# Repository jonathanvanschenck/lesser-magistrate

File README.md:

#  The Lesser Magistrate
A collection of Electrical and Mechanical Schematics for the IOC Lesser Magistrate Quizzing System

Schematics, PCB Files, BOM and 3D printing files are [available here](https://github.com/jonathanvanschenck/lesser-magistrate).

To find more information or get involved with Christian Bible Quizzing (CBQ), [click here](https://cbqz.org).

## Philosophy of Design
Heretofore, bible quizzing has had a fairly high barrier to entry; whether it be complicated rulebooks, distinct cultural practices or (of relevance here) expensive supplies. This project
seeks to address that third barrier by providing a low-cost, high-performance quizzing buzzer system, which can built by a reasonably competent individual. Unlike existing systems, we need
to meet the following design requirements:

  - Low cost and easily available parts
  - Easily manufactureable without special tooling
  - Is modular in design (e.g. individual components are easily and cheaply replaceable)
  - Can support up to 15 simultaneous participants

## Build Instructions
A Lesser Magistrate set can be built with a varying number of triggers depending on your needs. Throughout this documentation, examples are given for three common configurations:

- **16 triggers** — the maximum supported: 3 teams of 5 quizzers each, plus 1 trigger reserved for the quiz magistrate.
- **10 triggers** — the typical arrangement for a CBQ quiz: 3 teams of 3 quizzers each, plus 1 for the quiz magistrate.
- **12 triggers** — a 10-trigger set with 2 spares, useful to have on hand in case of hardware failure during a tournament.

If you have recieved a build kit, you should already have all the raw materials to build a lesser magistrate, including electrical components, 3d printed enclosures and hardware. In this case, you will only need a few tools to help during the build:
  - A Soldering Iron (literally anything will work here -- you don't need to spend tons of money on this unless you plan to make a lot of units)
  - Lead-free Solder (Again, literally anything will work here -- the amount of soldering on the project is pretty small so you won't run out)
  - Allen Wrench
  - Phillips head screw driver (long shaft)

### Video Guides and Examples

There is a video guide you can follow for step-by-step instructions on how to build your Lesser Magistrate system:

- https://www.youtube.com/watch?v=u-B20jy8v2o&list=PL-Vn05Kf5ezxIfupx7_Z1d6l5HKGBeLW2

Here are additional example videos:

- https://youtu.be/reuCWvhqvTU
- https://youtu.be/7Vi3QWguprs
- https://youtu.be/mlhh7Sf7_HU
- https://youtu.be/uHA6wKbFMOs
- https://youtu.be/KhpSTn409PQ
- https://youtu.be/kogF7mJOyTQ

### Electrical Schematics

All electrical schematics are available in the [graphics](./graphics) directory, which can be helpful during assembly, particularly for those who are more electrically inclined. They match the boards made from the [gerber files](./gerber).

There are some additional tools which are very helpful during the build process; but are not strictly necessary:
  - Some elmers glue, or similar light adhesive
  - The assembly jigs, [see the 3d printer directory for details](./3d)

If you are interested in purchasing a Lesser Magistrate system (or any of the necessary components -- particularly the PCBs), contact [the author](https://github.com/jonathanvanschenck).

If you did *not* receive a kit, the next section will explain how to acquire all the necessary raw components.

### Ordering the Components Yourself
If you did not receive kit, you will need to acquire the raw materials. Broadly there are 3 categories of things you will need to purchase:

#### 1. Electrical Component
You will need to buy all the electrical components (meaning chips, resistors, connectors and wires). See the [components README](./components/README.md) for full part lists and Digikey shopping links for 16, 12, and 10 trigger set configurations.

#### 2. PCB
You will also need to buy the actual PCBs to soulder everything to. You can find the gerber files (the extension is `.zip`) in the `gerber` directory, with a [README](./gerber/README.md) for details. Always order from these files: they are the released version of each board, and the README there lists each board's version. You can use any PCB manufacturer you prefer, for example [PCBWay](https://www.pcbway.com/) -- in every case you cant just upload your gerber files and the website will walk you through the steps. Two things to note: (1) make sure to select HASL lead-free surface treatment to avoid lead exposure, use defaults for everything else (2) you will likely be required to order at least 5 of every board; but the boards are sufficiently cheap that shipping is frequently the majority of the PCB cost even when over-buying boards.

#### 3. Plastic Enclosures
You will also need to get plastic enclosures for all the electrical elements. All of this is done with a 3d printer. Many schools and libraries have 3d printers available to the students/members, so try asking around in your community to see if someone has access to a printer to help with this piece. There are also plenty of online services that you can upload a file to and have them print and ship it to you. Though, if you plan on making more than, like, 2 of these units -- just get a printer yourself. They are pretty cheap these days, can you can do a lot with them. Both [Bambu Labs](https://bambulab.com/en-us) and [Prusa Reaserch](https://www.prusa3d.com/) have mid-level and high-end hobbyist models in the $500-$1500 range.

However you plan on getting your prints, you will need the STL files in the [stl](./stl) directory -- see the README there for details.

## Contributing and Development
The Lesser Magistrate is a fully open sourced project, and as such contribution is encouraged! As such PRs are more than welcome, and we would love to hear about [any issues](https://github.com/jonathanvanschenck/lesser-magistrate/issues) you may run into. Feature requests are also encouraged -- though keep in mind features will only be included in this project if they conform to the Philosophy of Design described above. Finally, if you take this project and do something cool with it (like adding extra features not suitable to this design philosophy), we would love to hear about it so that we can add a link to your work in the section below!

The electrical design was originally drawn in DipTrace and is now developed in [KiCad](https://www.kicad.org/), with one project per board in the [kicad](./kicad) directory (see its [README](./kicad/README.md), which also explains how each board is versioned and released). The files in [gerber](./gerber) are KiCad releases; the [gerber README](./gerber/README.md) says where to find the original DipTrace exports. We are also working on an SMD variant of the LM/LMM/Trigger boards so they can be assembled by a pick-and-place machine.

Developer tooling (KiCad design checks, a crosstalk simulation, the generated parts tables, a DigiKey part-search CLI, and a KiCad MCP server for AI-assisted board design with Claude Code) is described in [DEVELOPMENT.md](./DEVELOPMENT.md).

## Related Projects

## Deuteronomy 6:5-7
Love the Lord your God with all your heart and with all your soul and with all your strength.
These commandments that I give you today are to be on your hearts.
Impress them on your children. Talk about them when you sit at home and when you walk along the road, when you lie down and when you get up.

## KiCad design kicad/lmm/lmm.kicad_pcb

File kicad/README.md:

# KiCad Projects

The electrical design for the Lesser Magistrate, in KiCad 10. One project per board, plus one shared library:

```
kicad/
├── libraries/
│   ├── lesser-magistrate.kicad_sym   # symbols for the parts used on the boards
│   ├── lesser-magistrate.pretty/     # footprints for the parts used on the boards
│   └── lesser-magistrate.3dshapes/   # manufacturer 3D models KiCad doesn't ship
├── lm/        # LM: main quiz-magistrate controller board  (1 per set)
├── lmm/       # LMM: team module / breakout board          (1 per team)
└── trigger/   # Trigger: the quizzer's push button          (1 per quizzer)
```

Open a board with `kicad/<board>/<board>.kicad_pro`. KiCad allows one board per project, so boards that are
fabricated separately are separate projects that share a library. Each project's `sym-lib-table` and `fp-lib-table`
point at `${KIPRJMOD}/../libraries/`, so the project library resolves on any machine without setup. See
[DEVELOPMENT.md](../DEVELOPMENT.md#kicad) for installing KiCad.

## Libraries

**Use KiCad's stock libraries first.** They ship with KiCad, are maintained upstream, and most stock footprints come
with a 3D model. Add a part to the project library only when the stock libraries don't have it, or when its geometry
has to match a board that has already been built. Either way, KiCad embeds a copy of every symbol and footprint in
the schematic and board files, so a project still opens if a library changes or goes missing.

The current boards use the project library throughout, because their footprints reproduce the manufactured boards.
KiCad's stock DIP and resistor-array footprints have different drill sizes, for example (0.8 mm against 0.9 and
1.118 mm here). New designs should start from the stock libraries.

Symbols are named after the generic part (`C`, `LED`, `R_Network09`, `R_Pack04_SIP`, `74AC573`, `4072`, `74AC04`,
`RJ11`, `RJ45`, `USB_A`, `SW_Push`). `LED`, `RJ11` and `RJ45` use KiCad's stock drawings (the jack pins are numbered by
contact position, to match the footprints). Connectors are `J` (`JA1`-`JC1` are the team jacks on the LM). Footprints are named after the physical package or the specific part they were
drawn for (`RJ45_AdamTech_MTJ-881X1`, `DIP-20_W7.62mm`, …). Every placed part has:

- **Value**: the generic part, printed on the board and the BOM (e.g. `10nF`, `4072`, `74AC573`, `Green`)
- **MPN**: manufacturer part number
- **Datasheet**: the DigiKey product page

These match [components/README.md](../components/README.md), so KiCad's BOM export lists the ordering information
(see [Checks and outputs](#checks-and-outputs)).

The connector and mounting-hole footprints carry local pour clearances on their non-plated holes, which reproduces the
copper pour of the boards as manufactured.

### 3D models

Footprints reference KiCad's stock 3D models through `${KICAD10_3DMODEL_DIR}`, which a normal KiCad install sets.
Where no stock model of the exact part exists, the closest stock model with the same pin pattern stands in:

| Footprint | 3D model | Exact? |
|---|---|---|
| `DIP-14_W7.62mm`, `DIP-20_W7.62mm` | stock DIP-14 / DIP-20 | yes |
| `R_Array_SIP10`, `R_Array_SIP8` | stock SIP-10 / SIP-8 resistor array | yes |
| `LED_L513` | stock 5 mm LED (red; the parts are green and yellow) | close |
| `C_Kemet_C410` | stock 3.8 mm axial capacitor, squeezed from 7.5 mm to 6.5 mm pitch | close |
| `USB_A_OnShore_USB-A1HSW6` | Molex 67643 USB-A (same pin pattern) | close |
| `SW_Tactile_TS11-674_RA` | C&K PTS645 right-angle tactile switch (same pin pattern) | close |
| `RJ45_AdamTech_MTJ-881X1` | Adam Tech's model, in `lesser-magistrate.3dshapes/` | yes |
| `RJ11_Amphenol_54601-906001WPLF` | Amphenol's model, in `lesser-magistrate.3dshapes/` | yes |

Manufacturer models go in `libraries/lesser-magistrate.3dshapes/`, named after the footprint and referenced as
`${KIPRJMOD}/../libraries/lesser-magistrate.3dshapes/<name>.step`.

## Versions

Each board has its own version, because each is made separately: a new LM doesn't make a new LMM. A board's version
lives in one place, the `VERSION` text variable in its project file (`<board>.kicad_pro`; in KiCad, *Schematic Setup*
or *Board Setup* → *Project* → *Text Variables*). Everything that shows the version reads it from there as
`${VERSION}`:

- the silkscreen: `v${VERSION}` on LM's front, `LM Module v${VERSION}` on LMM's back, `Trigger v${VERSION}` on the
  Trigger's back
- the *Rev* field of each schematic and board title block, which appears on the schematic PDF

Versions are `major.minor.patch`, as in npm: **major** for a board that isn't a drop-in replacement (a different size,
connector or pinout), **minor** for a change to the circuit or copper, **patch** for silkscreen or other changes that
don't touch the circuit.

### Releasing a version

Release from a clean working tree, ideally on `master`:

```sh
node tools/release/release.mjs status              # each board's version, tag and fab files
node tools/release/release.mjs bump lm minor       # or major, patch, or an exact version: bump lm 1.1.0
git push origin master && git push origin lm@1.1.0
```

`bump` does everything a release needs, and undoes its changes if any step fails:

1. sets `VERSION` in the board's project file
2. runs that board's design checks (`tools/kicad/check.sh <board>`: its ERC and DRC, the crosstalk simulation for LM,
   the BOM tables). They run with the new version in place, so the version text is checked on the silkscreen too. If
   they fail, nothing is exported, committed or tagged.
3. exports the board's fab files and replaces its zip in [`gerber/`](../gerber): gerbers, drill file and an
   IPC-D-356 netlist (which board makers use for electrical testing), and a `README.txt` naming the board and
   version. Every file name inside carries the version (`lm-1.1.0-F_Cu.gtl`), so a downloaded zip says what it is.
4. exports the schematic to `graphics/<board>-schematic.pdf`
5. updates the version table in [`gerber/README.md`](../gerber/README.md)
6. commits those files as `<board>: version <x.y.z>`, and tags that commit `<board>@<x.y.z>` (e.g. `lm@1.1.0`)

It never pushes. If you release from a branch, merge it with a merge commit, not a squash or rebase, so the tag stays on
a commit that's on `master`.

The repo's older tags (`0.4.0` to `1.0.0`) versioned the whole repo, enclosures included. Board tags carry the board's
name, so they don't collide with them or with each other.

**A second, design-for-manufacture board line** (the planned SMD revision) fits the same scheme if it lives in its own
directory with its own board names, e.g. `kicad-dfm/lm-dfm/`, tagged `lm-dfm@1.0.0`: add its boards to `BOARDS` in
`tools/release/release.mjs`. On a separate long-lived branch instead, its tags would still share the repo's one tag
namespace, so it would need distinct board names anyway, and fixes would have to be merged between the branches. A
directory is the simpler of the two.

## Checks and outputs

`tools/kicad/check.sh` runs ERC and DRC (with schematic/board parity) on every board, or on the boards you name. It
fails on any error that hasn't been excluded in KiCad, and reports warnings without failing. A board takes about 5 s;
checking LM also runs the crosstalk simulation, about 10 s more. The same script runs in CI
([.github/workflows/kicad.yml](../.github/workflows/kicad.yml)) on every push or pull request that touches the boards,
the simulation, the parts catalogue or the tooling.

```sh
tools/kicad/check.sh              # all boards
tools/kicad/check.sh lm           # one board
tools/kicad/check.sh --fab        # also gerbers, drill, BOM (CSV), schematic PDF and a 3D render
```

Reports (`erc.json`, `drc.json`) and outputs go to `build/kicad/<board>/`, which git ignores. CI uploads the same folder as the
`kicad-outputs` artifact.

**Known issues that fail the check:** a violation that's understood and accepted should be *excluded* in KiCad, with a
comment saying why (right-click the marker in the ERC or DRC dialog, *Exclude*). Exclusions are saved in the
`.kicad_pro` file, so the check and CI skip them too. There are no exclusions at the moment: all three boards pass.

**Fabrication files:** the gerbers `--fab` writes are for review. The files to order are the released ones in
[`gerber/`](../gerber), which `release.mjs bump` writes (see [Releasing a version](#releasing-a-version)). The table in
[`gerber/README.md`](../gerber/README.md) gives each one's version.

## Migration from DipTrace

LM and LMM were exported from DipTrace 5.3.5 (Eagle XML), imported with KiCad's Eagle importer, and then cleaned up.
Trigger's DipTrace source (`buzzer_pcb.dip`) was lost, so it was rebuilt from the fab files in `TriggerGerber.zip`: the
placement file, the IPC-D-356 pad netlist, the drill file and the copper/outline gerbers. The DipTrace sources were
removed from the repo after the migration; they're in git history before that commit.

What was verified for each board, against the original DipTrace netlists and the manufactured gerbers:

| Check | LM | LMM | Trigger |
|---|---|---|---|
| Schematic connectivity = DipTrace netlist | 74/74 nets | 6/6 nets | 2/2 nets (from IPC-D-356) |
| Board connectivity = DipTrace netlist | 74/74 nets | 6/6 nets | 2/2 nets |
| Schematic ↔ board parity (KiCad DRC) | clean | clean | clean |
| Drill holes vs `Through.drl` | 280/280 within 0.002 mm | 34/34 | 9/9 |
| Board outline | identical | identical | identical |
| Top copper and solder mask vs gerbers | ≤ 1.3 mm² differs | ≤ 0.5 mm² | ≤ 0.4 mm² |

Known differences from the manufactured boards (none of them electrical):

- **Bottom copper pour (LM)**: KiCad's refill puts about 130 mm² more ground copper than DipTrace did, mostly in narrow
  gaps between pads. DipTrace filled with a 0.635 mm stroke and couldn't reach them. Clearances are unchanged.
- **Silkscreen text** is placed, sized and stroked like the manufactured boards (rebuilt from the Eagle export, using
  Eagle's rule that turns upside-down text the right way up). KiCad's font is slightly wider than DipTrace's. Text that
  DipTrace printed upside down now reads upright in the same spot. The chips are labelled with their part type
  (`4072`, `74AC04`, `74AC573`) where DipTrace printed `OR`, `NOT` and `Octal D-Latch`. Multi-line titles are
  split into one text per line, because KiCad's 3D renderer and gerber plotter space multi-line text differently.
- **Mounting holes** are footprints `H1`–`H4`, marked board-only, so they're on the board but not in the schematic.

Schematic cleanup after the import (connectivity unchanged):

- LM: net labels moved off the pins onto the ends of their wire stubs, no-connect flags on intentionally unused pins,
  `PWR_FLAG`s where 5V and GND enter from the USB connector, pin names hidden on symbols whose pin names were just
  their numbers, everything on KiCad's 50 mil grid, the latch-enable wire rerouted so it no longer crosses U2, and
  every reference designator visible (the filter capacitors C4-C18 show their reference, with a note giving their
  value).
- Boards moved to the middle of their pages (LM's Eagle import had put it off the page); every fab layer moved by the
  same exact offset and is otherwise unchanged.
- All three: jacks drawn with the stock-style symbols, each pin a short wire and a named net (`5V`, `TRIG_A1`–`TRIG_C5`
  and `ARM` on the LM, `TRIG1`–`TRIG5` on the LMM, `TRIG` on the Trigger); drawings centred on their sheets.
- Wire colours: DipTrace's net colours didn't survive the export, so they were re-derived from the circuit. Each
  trigger's signal is coloured from its jack, through its series resistor and latch, to its LED, with the same colour
  for trigger *k* on the LM and the LMM; the arm button and latch-enable nets have their own colours. The colours are
  stored on each wire, so a new wire needs its colour set by hand (right-click → *Properties*). Each schematic has a
  legend.

## Fixes since the DipTrace design

ERC and DRC found two problems in LM as manufactured. Both are fixed in the schematic and on the board. The
silkscreen was also cleaned up on all three boards, and the first KiCad releases (LM 1.1.0, LMM 1.1.0, Trigger 1.0.1)
tidied some routing. None of this changes how the boards work:

- **Floating inputs (ERC, 4 errors):** the three unused inverters in U8 (CD74AC04E, inputs A1–A3) and latch input
  U2 D8 were left floating. A floating CMOS input can drift to mid-supply and make its gate draw current or oscillate.
  They're now tied to GND: U8 pins 1, 3 and 5 by a back-side track to pin 7, and U2 pin 9 by a back-side track to
  pin 10.
- **Clearance (DRC, 3 errors):** the 5V track ran diagonally into pad 1 of each RJ45 (JA1, JB1, JC1), passing 0.18 mm
  from the unconnected pad 3. The design rule is 0.2032 mm (8 mil). The track now runs along the 5V bus to above pad 1
  and drops straight down, about 0.9 mm from pad 3.
- **Silkscreen (DRC warnings):** the connector outlines (J2, the RJ45s and RJ11s, and the Trigger's button) ran past
  the board edge and, on the RJ11s, over the plastic locating-peg holes. They now stop about 0.25 mm inside the edge
  and leave a gap around the holes, in the library footprints and on every board. Six labels that overlapped
  another label, an outline or a pad were moved: C1, C2 and C3 (now on the far side of their capacitor from the
  chip), RB1, and the Trigger's J1 reference and value.
- **Routing (LM 1.1.0, LMM 1.1.0):** on LM, the 5V track was reshaped in three places and the bottom ground bus moved
  up 0.66 mm; on LMM, the five trigger lines were rerouted, three of them on the other copper layer. No connection
  changed. Labels were moved and the board version is printed on each board's silkscreen.

The ground pour was refilled after these changes. The only remaining warnings are 23 small isolated copper islands in
LM's ground pour, which don't affect function.

## Next revision

Changes planned for the next LM revision (the SMD variant). None of them are in the current boards.

### Power and decoupling

The LM draws little power. Each LED takes about (5 V − 2.1 V) / 150 Ω ≈ 19 mA, and normally one LED is lit: the
yellow light while armed, then the winner's green light. A tie lights more, and the worst case, every LED at once, is
about 0.3 A, within USB 2.0's 500 mA. The 1.524 mm 5V track drops about 20 mV at that current, so track width isn't
the limit. A USB port or a long, thin cable loses more than the board does.

The weak point is decoupling. LM has six logic chips but only three 1 µF capacitors (C1–C3), 15–30 mm from the chips,
and none near the three CD4072s (U3, U5, U6). When a latch output switches an LED, the current step pulls a chip's
supply down and lifts its ground for a moment, which can cause a false or missed latch. The next revision should
have:

- **A 100 nF ceramic capacitor (X7R) at every chip**, between its VCC and GND pins, within about 3 mm of the VCC pin,
  with short, direct tracks or vias to the ground pour.
- **A 10–47 µF bulk capacitor where USB power enters** (J2), to supply LED switching current and smooth out a long
  USB cable. The existing 1 µF capacitors can go.
- **Solid ground pours on both layers**, stitched together with vias. The current pour has 23 isolated islands.
- **The 5V track at 0.5 mm or wider**: plenty for 0.3 A, so routing space isn't wasted on a wider track.

These will be enforced by checks (see [DEVELOPMENT.md](../DEVELOPMENT.md#planned)): a power budget computed from the
schematic, and a capacitor near every chip on the board.

### Battery power (option)

Not committed to; an option if a set needs to run without a computer or USB charger. Only the LM changes: the LMMs
and triggers take their 5V from the LM through the cables. At the steady ~20 mA above, batteries last a long time.

- **No change: a USB power bank** on the existing A-to-A cable. Many power banks switch off when the load is below
  about 50–100 mA, which would cut out mid-quiz, so it needs one with an "always on" or low-current mode. Test a
  bank before relying on it.
- **Built in: 4 × AA NiMH rechargeable cells** (about 2000 mAh, so roughly 100 hours). They start near 5.6 V fully
  charged, inside the 74AC chips' 6 V limit, and stay around 4.8–5 V for most of their discharge. The board needs a
  battery holder, an on/off switch, and a Schottky diode or P-channel MOSFET on each source so USB and the battery
  can't feed into each other; about $3–5 of parts. The bigger job is a battery compartment in the 3D-printed
  enclosure. The cells are charged outside the box.
- **Not recommended:**
  - 3 × AA alkaline works, but the supply sags from 4.5 V to about 3.3 V as they drain: the LEDs dim and the CD4072s
    slow down, widening the tie window.
  - 4 × AA alkaline starts at about 6.4 V, above the 74AC chips' limit.
  - A built-in lithium cell needs a charger chip and protection circuit, fine-pitch parts and shipping rules, which
    doesn't fit the hand-built, low-cost design.

If the battery option goes ahead, the crosstalk simulation's supply voltage (fixed at 5 V in `sim/crosstalk.py`)
should become a parameter, and the check should also run at the lowest battery voltage, since the noise margins
shrink with the supply.

### Trigger cable

TRIG3 and TRIG5 share a twisted pair in the Cat5 cable, which makes them the worst case for crosstalk (see
[sim/README.md](../sim/README.md)). Giving each trigger its own pair, or using a spare wire as a ground, would cut the
coupling at its source. That changes the LMM and LM jack wiring, so it would need a new LMM too.

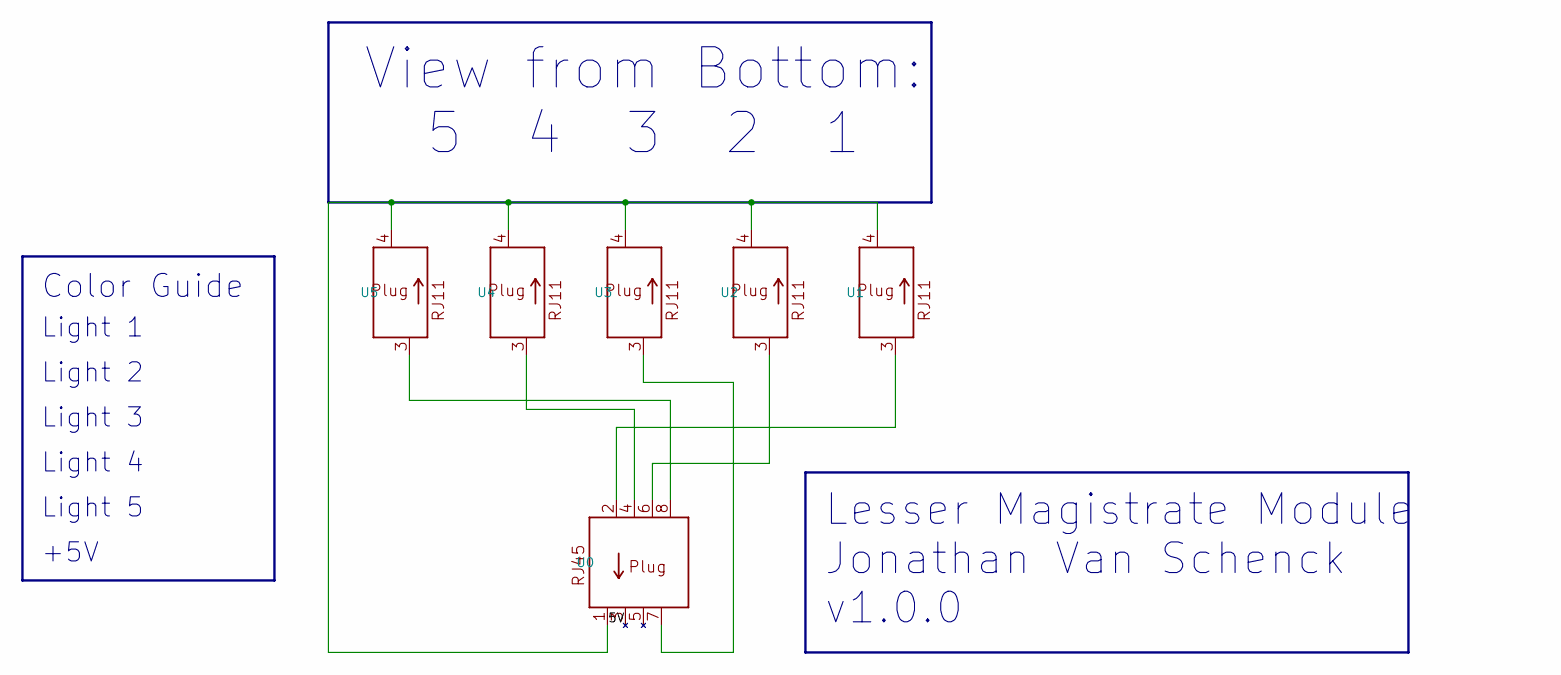
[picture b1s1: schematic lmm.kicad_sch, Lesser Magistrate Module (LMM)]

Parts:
U0: RJ45; RJ45_AdamTech_MTJ-881X1; MPN MTJ-881X1
U1, U2, U3, U4, U5: RJ11; RJ11_Amphenol_54601-906001WPLF; MPN 54601-906001WPLF

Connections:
/5V: U0.1, U1.4, U2.4, U3.4, U4.4, U5.4
unnamed: U0.2, U1.3
unnamed: U0.4, U4.3
unnamed: U0.6, U2.3
unnamed: U0.7, U3.3
unnamed: U0.8, U5.3

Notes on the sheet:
Lesser Magistrate Module Jonathan Van Schenck v1.0.0
Color Guide
Light 5
+5V
Light 2
View from Bottom: 5 4 3 2 1
Light 3
Light 4
Light 1

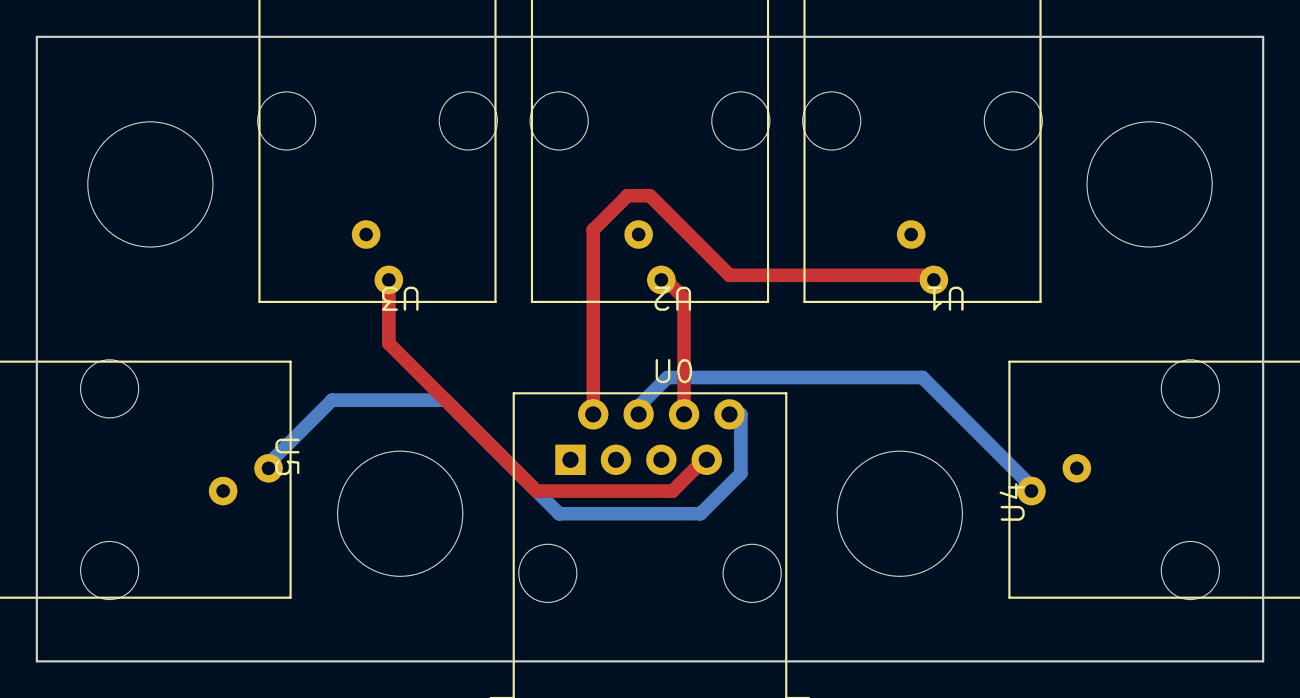
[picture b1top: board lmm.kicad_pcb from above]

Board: 2 copper layers, 68.6 x 34.9 mm, 10 parts (0 on the bottom side), 6 nets.

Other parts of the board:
H1, H2, H3, H4: MountingHole_7.0mm

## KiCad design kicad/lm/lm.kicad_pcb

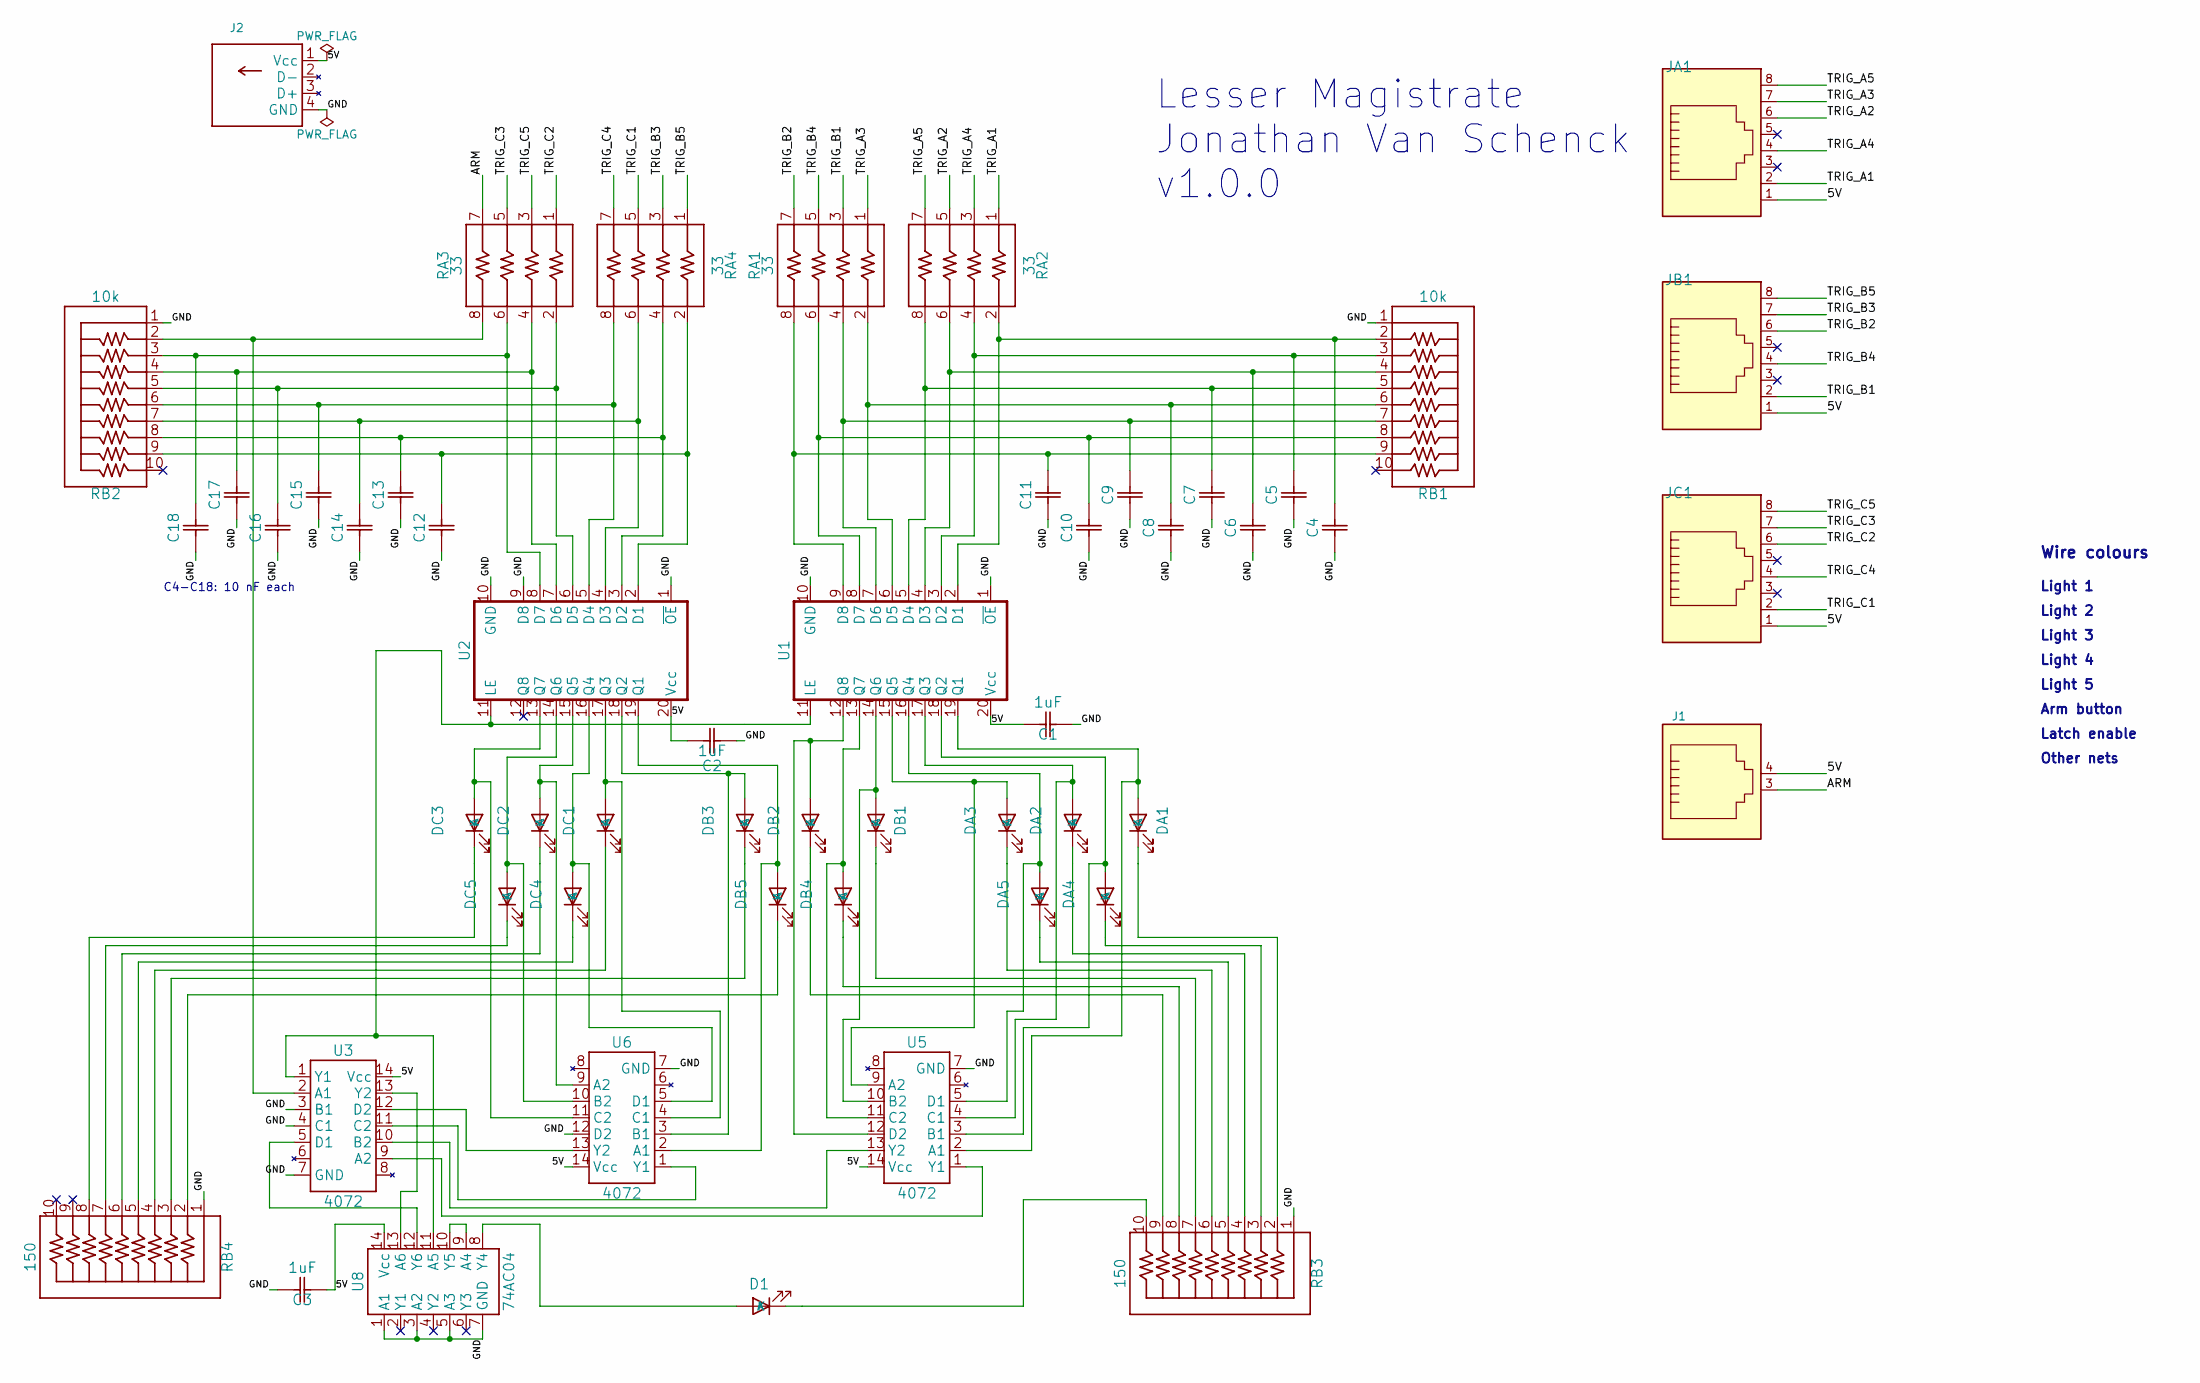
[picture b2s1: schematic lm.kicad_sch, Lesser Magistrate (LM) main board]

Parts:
C1, C2, C3: 1uF; C_Kemet_C410; MPN C410C105K3R5TA
C4, C5, C6, C7, C8, C9, C10, C11, C12, C13, C14, C15, C16, C17, C18: 10nF; C_Kemet_C410; MPN C410C103K5R5TA
D1: Yellow; LED_L513; MPN L513YD-C
DA1, DA2, DA3, DA4, DA5: Green; LED_L513; MPN L513GD-B
DB1, DB2, DB3, DB4, DB5: Green; LED_L513; MPN L513GD-B
DC1, DC2, DC3, DC4, DC5: Green; LED_L513; MPN L513GD-B
J1: RJ11; RJ11_Amphenol_54601-906001WPLF; MPN 54601-906001WPLF
J2: USB_A; USB_A_OnShore_USB-A1HSW6; MPN USB-A1HSW6
JA1: RJ45; RJ45_AdamTech_MTJ-881X1; MPN MTJ-881X1
JB1: RJ45; RJ45_AdamTech_MTJ-881X1; MPN MTJ-881X1
JC1: RJ45; RJ45_AdamTech_MTJ-881X1; MPN MTJ-881X1
RA1, RA2, RA3, RA4: 33; R_Array_SIP8; MPN 4608X-102-330LF
RB1, RB2: 10k; R_Array_SIP10; MPN 4610X-101-103LF
RB3, RB4: 150; R_Array_SIP10; MPN 4610X-101-151LF
U1, U2: 74AC573; DIP-20_W7.62mm; MPN SN74AC573N
U3, U5, U6: 4072; DIP-14_W7.62mm; MPN CD4072BE
U8: 74AC04; DIP-14_W7.62mm; MPN CD74AC04E

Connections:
/5V: C1.1, C2.1, C3.1, J1.4, J2.1 (Vcc), JA1.1, JB1.1, JC1.1, U1.20 (Vcc), U2.20 (Vcc), U3.14 (Vcc), U5.14 (Vcc), U6.14 (Vcc), U8.14 (Vcc)
/ARM: J1.3, RA3.7
/GND: C1.2, C2.2, C3.2, C4.1, C5.1, C6.1, C7.1, C8.1, C9.1, C10.1, C11.1, C12.1, C13.1, C14.1, C15.1, C16.1, C17.1, C18.1, J2.4 (GND), RB1.1, RB2.1, RB3.1, RB4.1, U1.1 (~OE), U1.10 (GND), U2.1 (~OE), U2.9 (D8), U2.10 (GND), U3.3 (B1), U3.4 (C1), U3.7 (GND), U5.7 (GND), U6.7 (GND), U6.12 (D2), U8.1 (A1), U8.3 (A2), U8.5 (A3), U8.7 (GND)
/TRIG_A1: JA1.2, RA2.1
/TRIG_A2: JA1.6, RA2.5
/TRIG_A3: JA1.7, RA1.1
/TRIG_A4: JA1.4, RA2.3
/TRIG_A5: JA1.8, RA2.7
/TRIG_B1: JB1.2, RA1.3
/TRIG_B2: JB1.6, RA1.7
/TRIG_B3: JB1.7, RA4.3
/TRIG_B4: JB1.4, RA1.5
/TRIG_B5: JB1.8, RA4.1
/TRIG_C1: JC1.2, RA4.5
/TRIG_C2: JC1.6, RA3.1
/TRIG_C3: JC1.7, RA3.5
/TRIG_C4: JC1.4, RA4.7
/TRIG_C5: JC1.8, RA3.3
unnamed: D1.2 (A), U8.8 (Y4)
unnamed: D1.1 (K), RB3.10
unnamed: DA1.2 (A), U1.19 (Q1), U5.2 (A1)
unnamed: DA1.1 (K), RB3.2
unnamed: DA2.2 (A), U1.17 (Q3), U5.4 (C1)
unnamed: DA2.1 (K), RB3.4
unnamed: DA3.2 (A), U1.15 (Q5), U5.9 (A2)
unnamed: DA3.1 (K), RB3.6
unnamed: DA4.2 (A), U1.18 (Q2), U5.3 (B1)
unnamed: DA4.1 (K), RB3.3
unnamed: DA5.2 (A), U1.16 (Q4), U5.5 (D1)
unnamed: DA5.1 (K), RB3.5
unnamed: DB1.2 (A), U1.14 (Q6), U5.10 (B2)
unnamed: DB1.1 (K), RB3.7
unnamed: DB2.2 (A), U1.12 (Q8), U5.12 (D2)
unnamed: DB2.1 (K), RB3.9
unnamed: DB3.2 (A), U2.18 (Q2), U6.3 (B1)
unnamed: DB3.1 (K), RB4.3
unnamed: DB4.2 (A), U1.13 (Q7), U5.11 (C2)
unnamed: DB4.1 (K), RB3.8
unnamed: DB5.2 (A), U2.19 (Q1), U6.2 (A1)
unnamed: DB5.1 (K), RB4.2
unnamed: DC1.2 (A), U2.17 (Q3), U6.4 (C1)
unnamed: DC1.1 (K), RB4.4
unnamed: DC2.2 (A), U2.15 (Q5), U6.9 (A2)
unnamed: DC2.1 (K), RB4.6
unnamed: DC3.2 (A), U2.13 (Q7), U6.11 (C2)
unnamed: DC3.1 (K), RB4.8
unnamed: DC4.2 (A), U2.16 (Q4), U6.5 (D1)
unnamed: DC4.1 (K), RB4.5
unnamed: DC5.2 (A), U2.14 (Q6), U6.10 (B2)
unnamed: DC5.1 (K), RB4.7
unnamed: C4.2, RA2.2, RB1.2, U1.2 (D1)
unnamed: C5.2, RA2.4, RB1.3, U1.3 (D2)
unnamed: C6.2, RA2.6, RB1.4, U1.4 (D3)
unnamed: C7.2, RA2.8, RB1.5, U1.5 (D4)
unnamed: C8.2, RA1.2, RB1.6, U1.6 (D5)
unnamed: C9.2, RA1.4, RB1.7, U1.7 (D6)
unnamed: C10.2, RA1.6, RB1.8, U1.8 (D7)
unnamed: C11.2, RA1.8, RB1.9, U1.9 (D8)
unnamed: U1.11 (LE), U2.11 (LE), U3.1 (Y1), U8.11 (A5)
unnamed: C12.2, RA4.2, RB2.9, U2.2 (D1)
unnamed: C13.2, RA4.4, RB2.8, U2.3 (D2)
unnamed: C14.2, RA4.6, RB2.7, U2.4 (D3)
unnamed: C15.2, RA4.8, RB2.6, U2.5 (D4)
unnamed: C16.2, RA3.2, RB2.5, U2.6 (D5)
unnamed: C17.2, RA3.4, RB2.4, U2.7 (D6)
unnamed: C18.2, RA3.6, RB2.3, U2.8 (D7)
unnamed: RA3.8, RB2.2, U3.2 (A1)
unnamed: U3.9 (A2), U5.1 (Y1)
unnamed: U3.10 (B2), U5.13 (Y2)
unnamed: U3.11 (C2), U6.1 (Y1)
unnamed: U3.5 (D1), U8.12 (Y6)
unnamed: U3.12 (D2), U6.13 (Y2)
unnamed: U3.13 (Y2), U8.13 (A6)
unnamed: U8.9 (A4), U8.10 (Y5)

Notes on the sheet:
Lesser Magistrate Jonathan Van Schenck v1.0.0
Wire colours
Light 1
Light 2
Light 3
Light 4
Light 5
Arm button
Latch enable
Other nets
C4-C18: 10 nF each

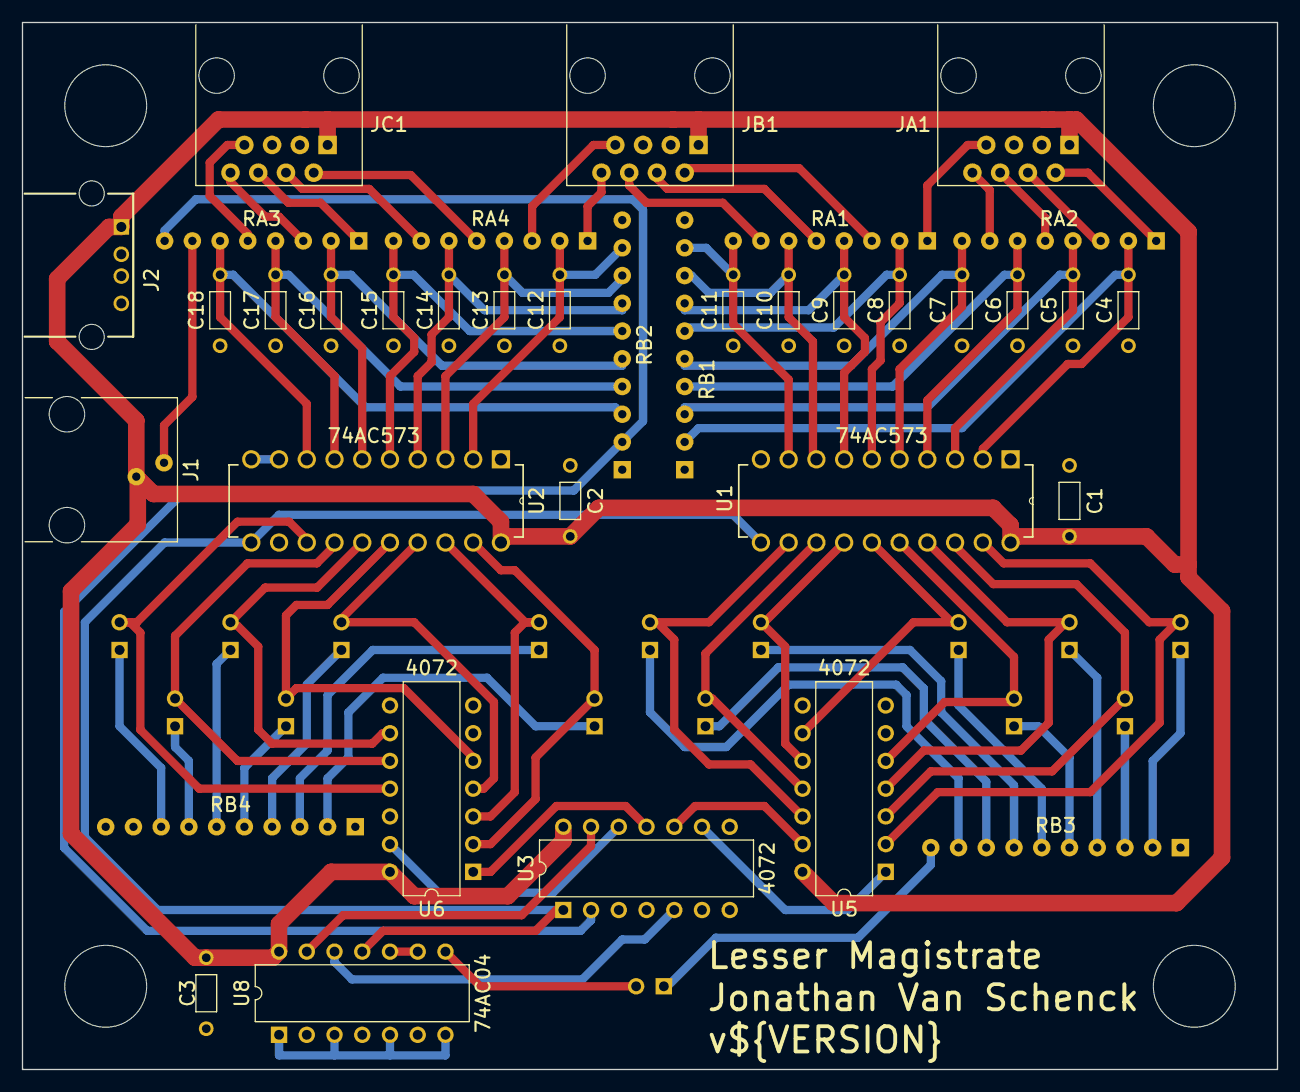
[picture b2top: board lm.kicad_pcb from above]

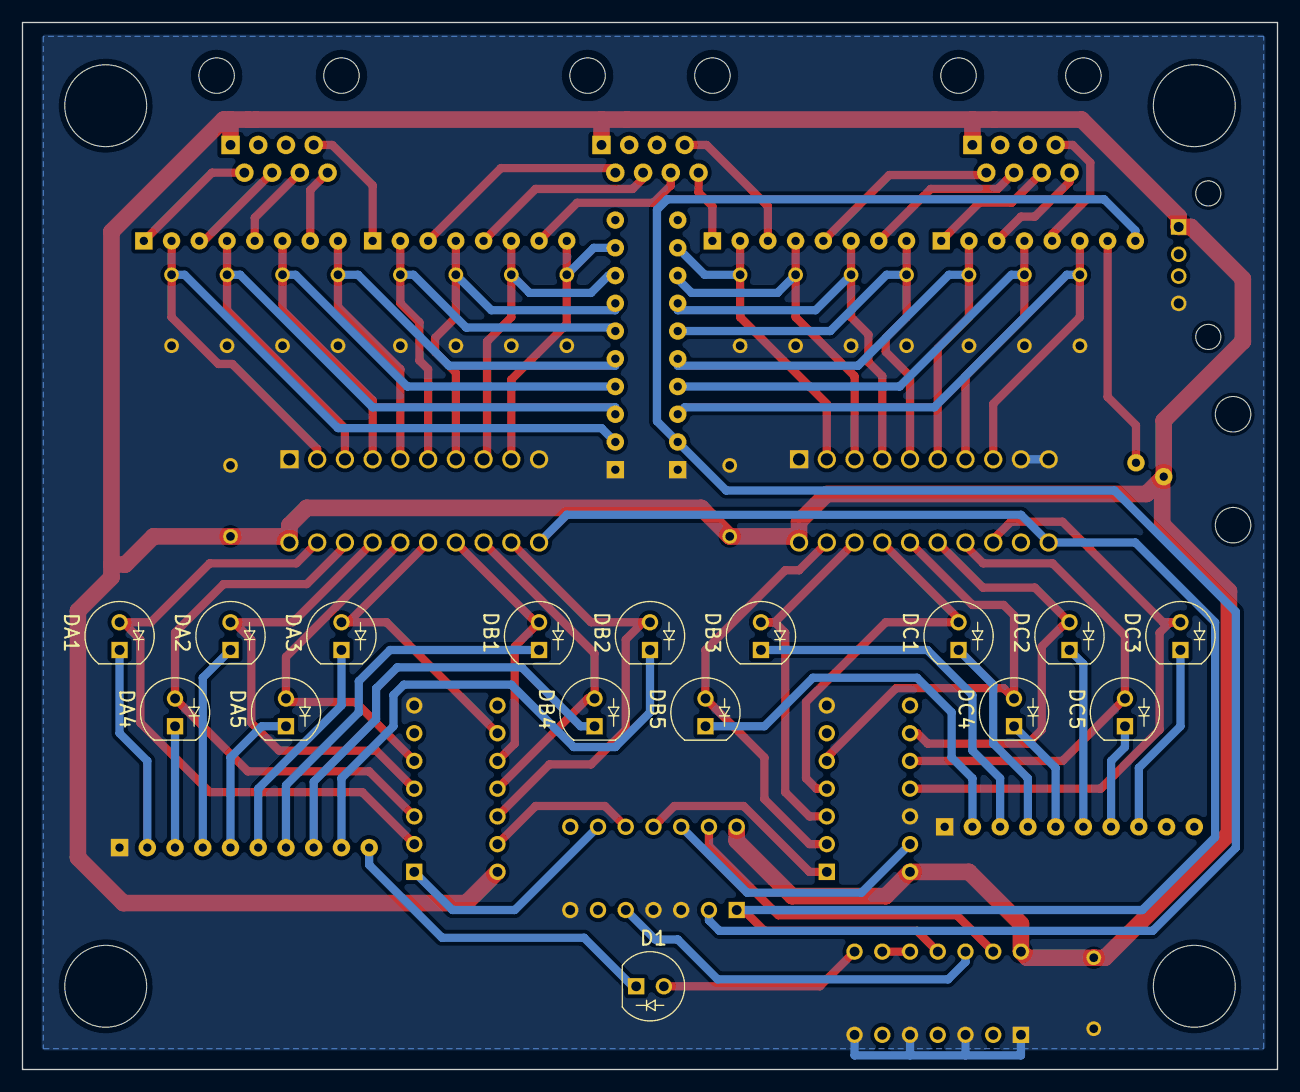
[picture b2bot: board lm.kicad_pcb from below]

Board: 2 copper layers, 114.9 x 95.9 mm, 57 parts (16 on the bottom side), 74 nets.

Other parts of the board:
H1, H2, H3, H4: MountingHole_7.5mm
